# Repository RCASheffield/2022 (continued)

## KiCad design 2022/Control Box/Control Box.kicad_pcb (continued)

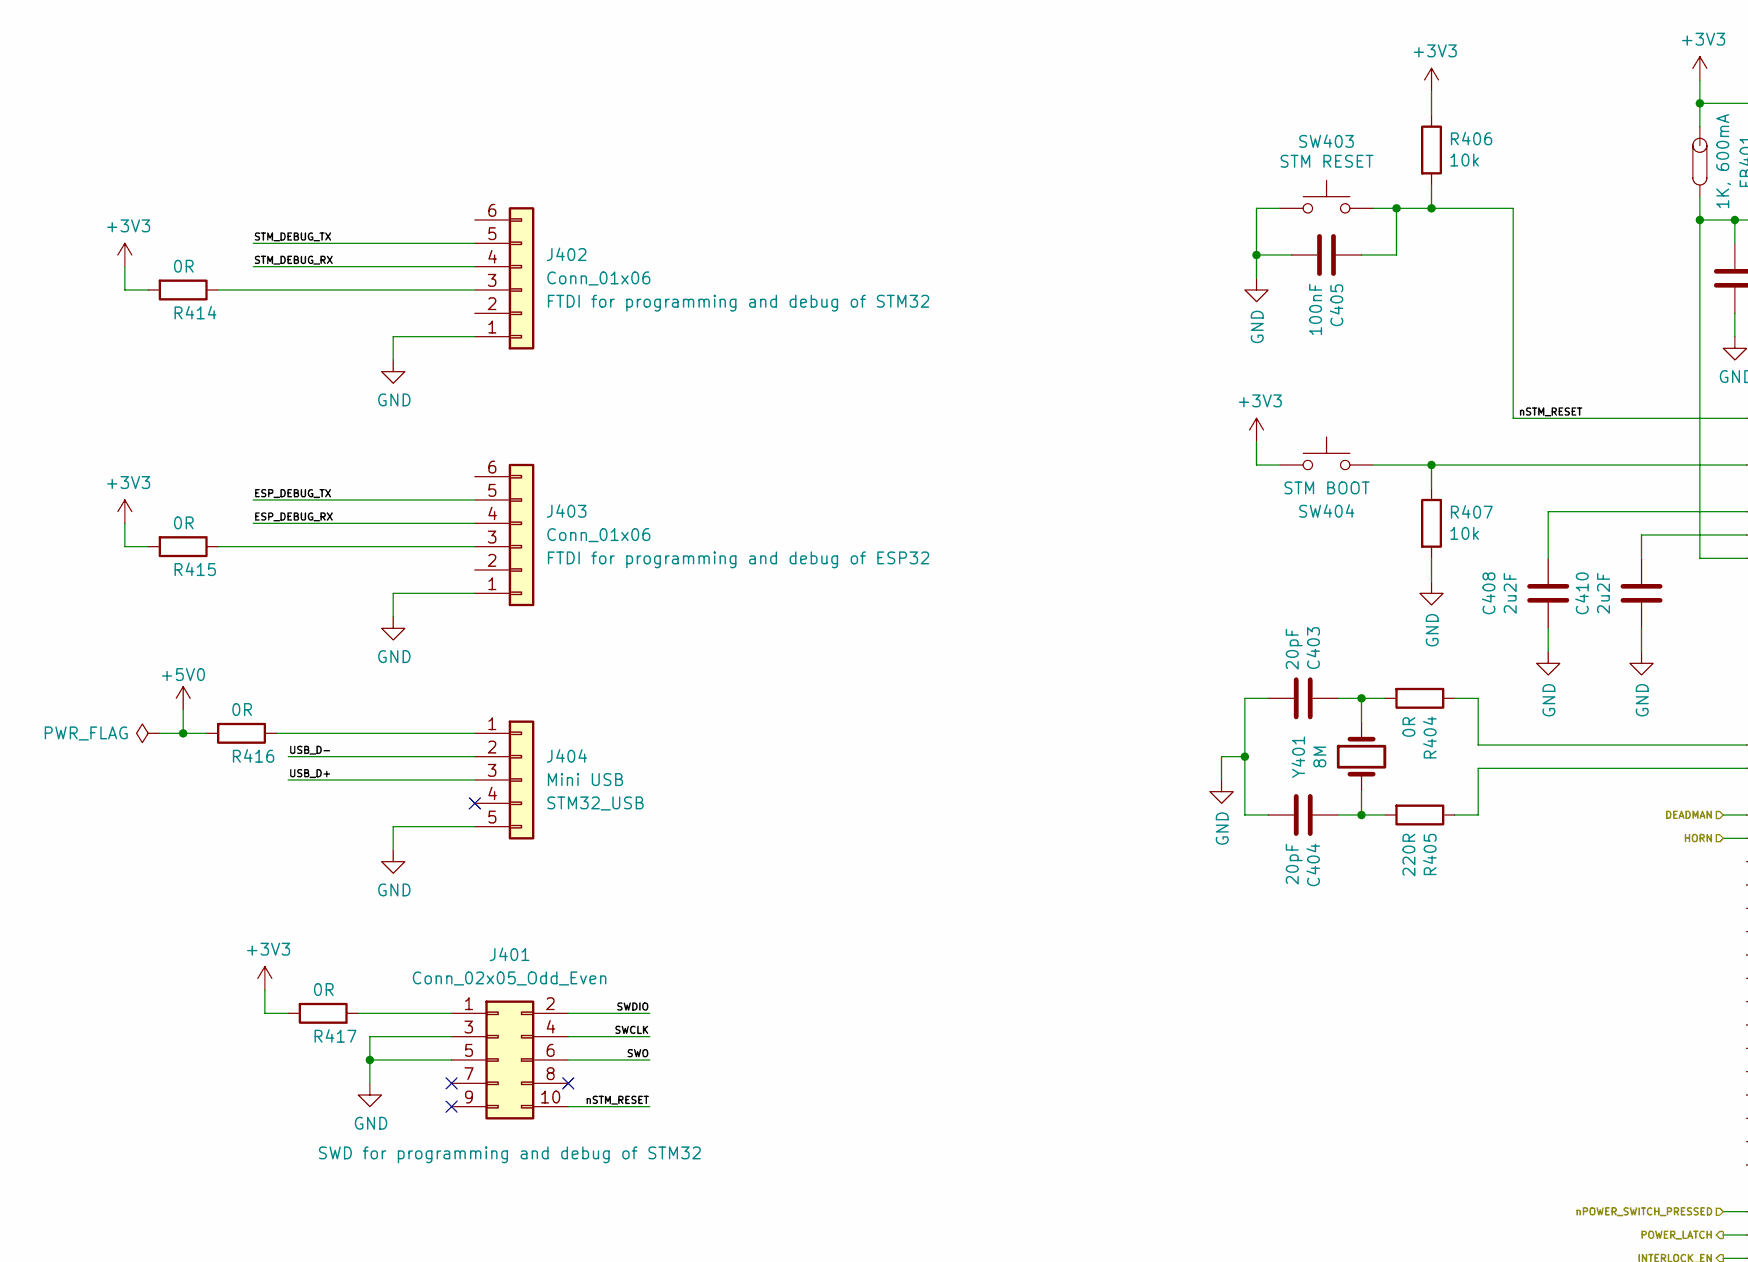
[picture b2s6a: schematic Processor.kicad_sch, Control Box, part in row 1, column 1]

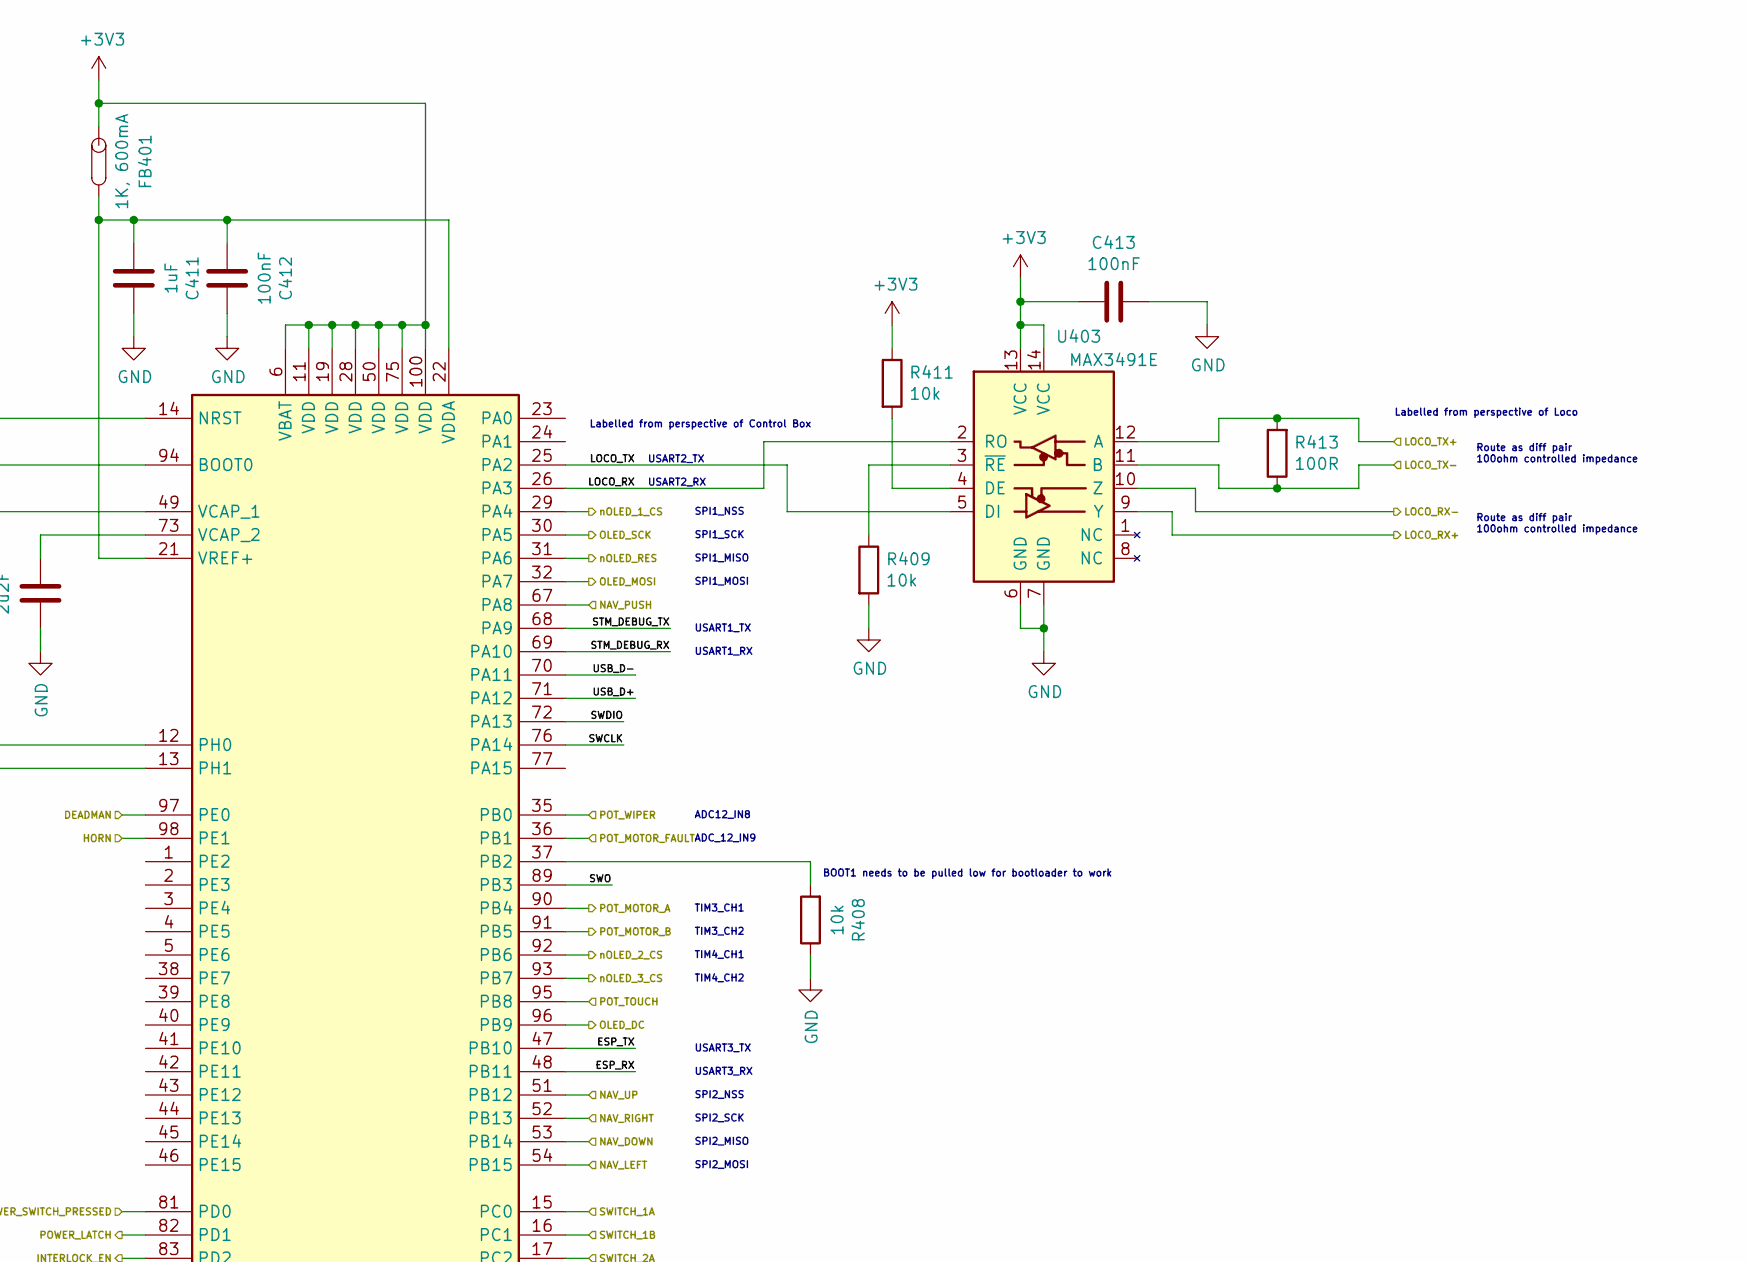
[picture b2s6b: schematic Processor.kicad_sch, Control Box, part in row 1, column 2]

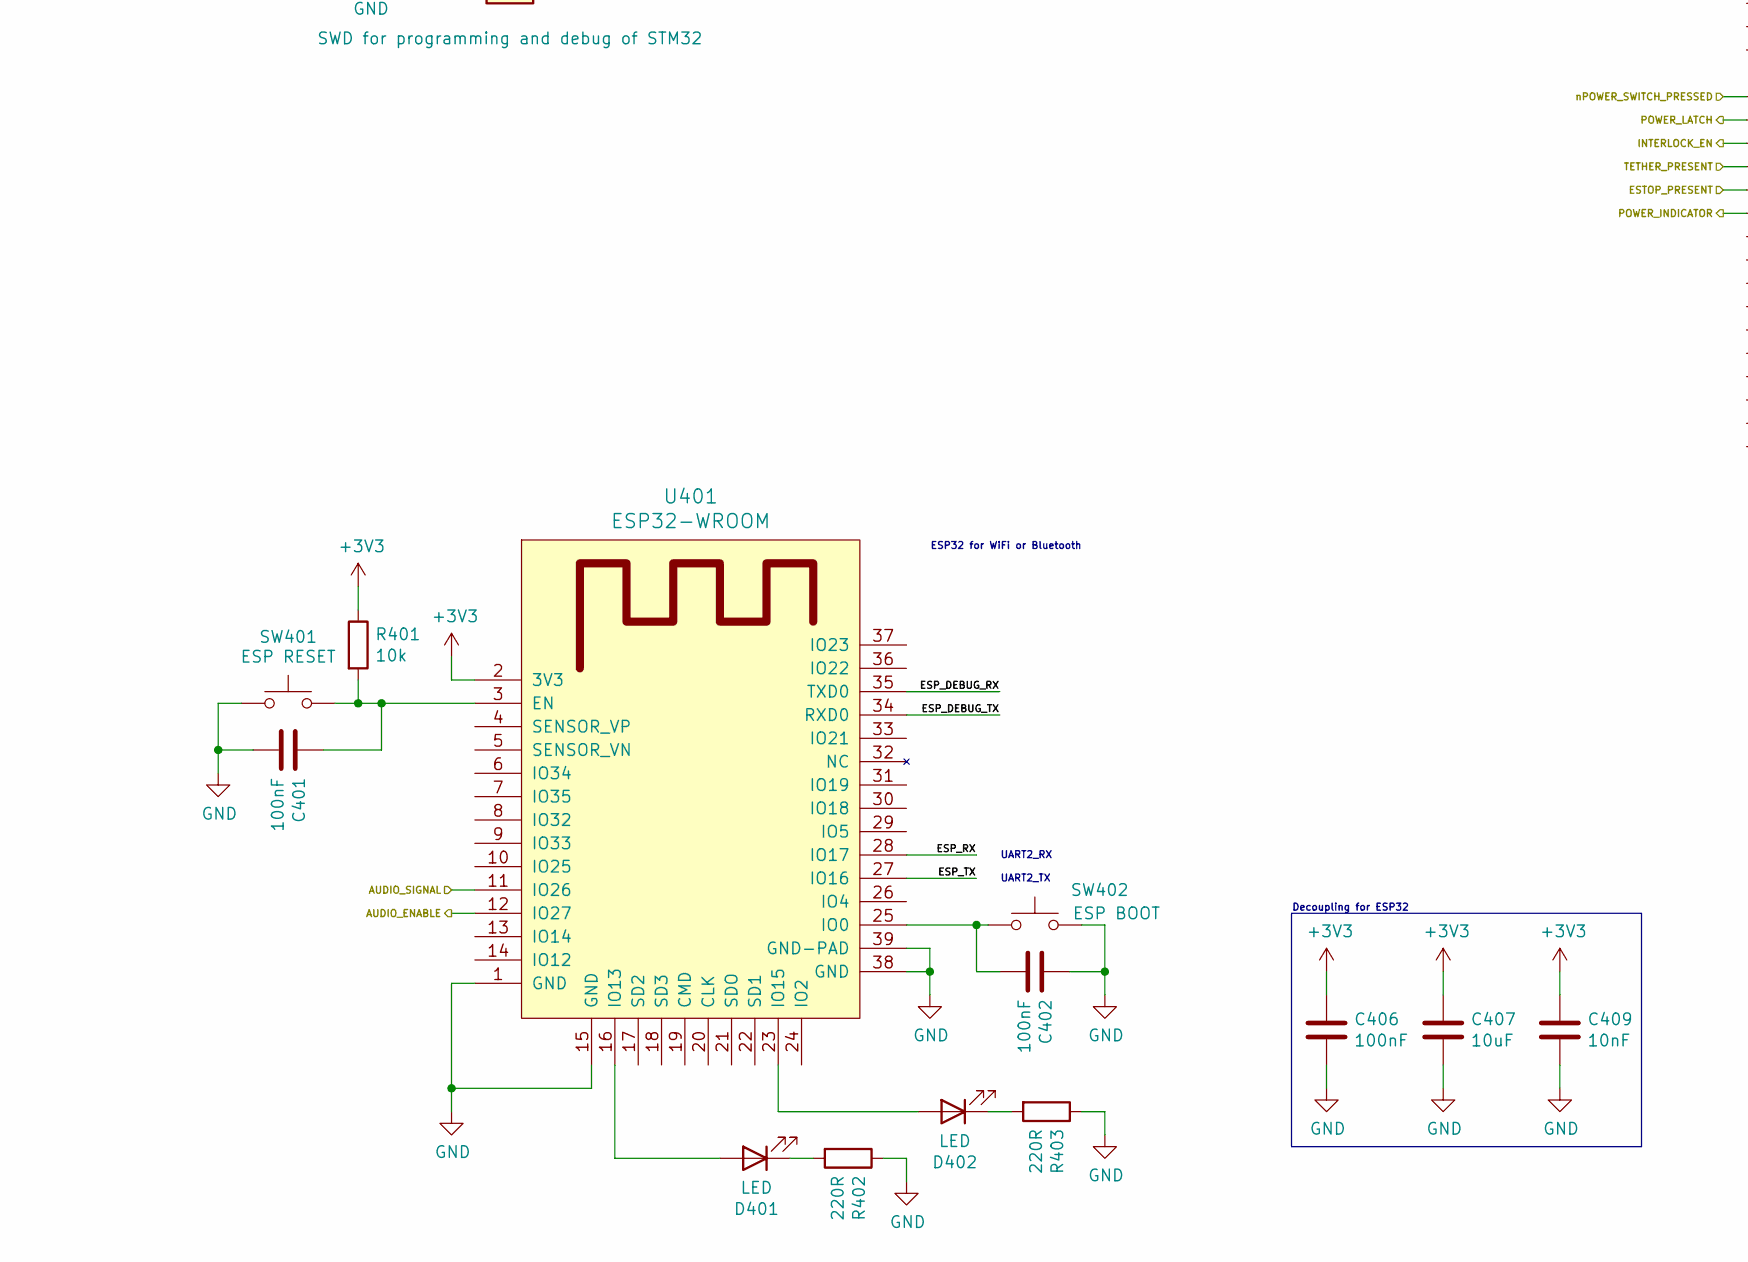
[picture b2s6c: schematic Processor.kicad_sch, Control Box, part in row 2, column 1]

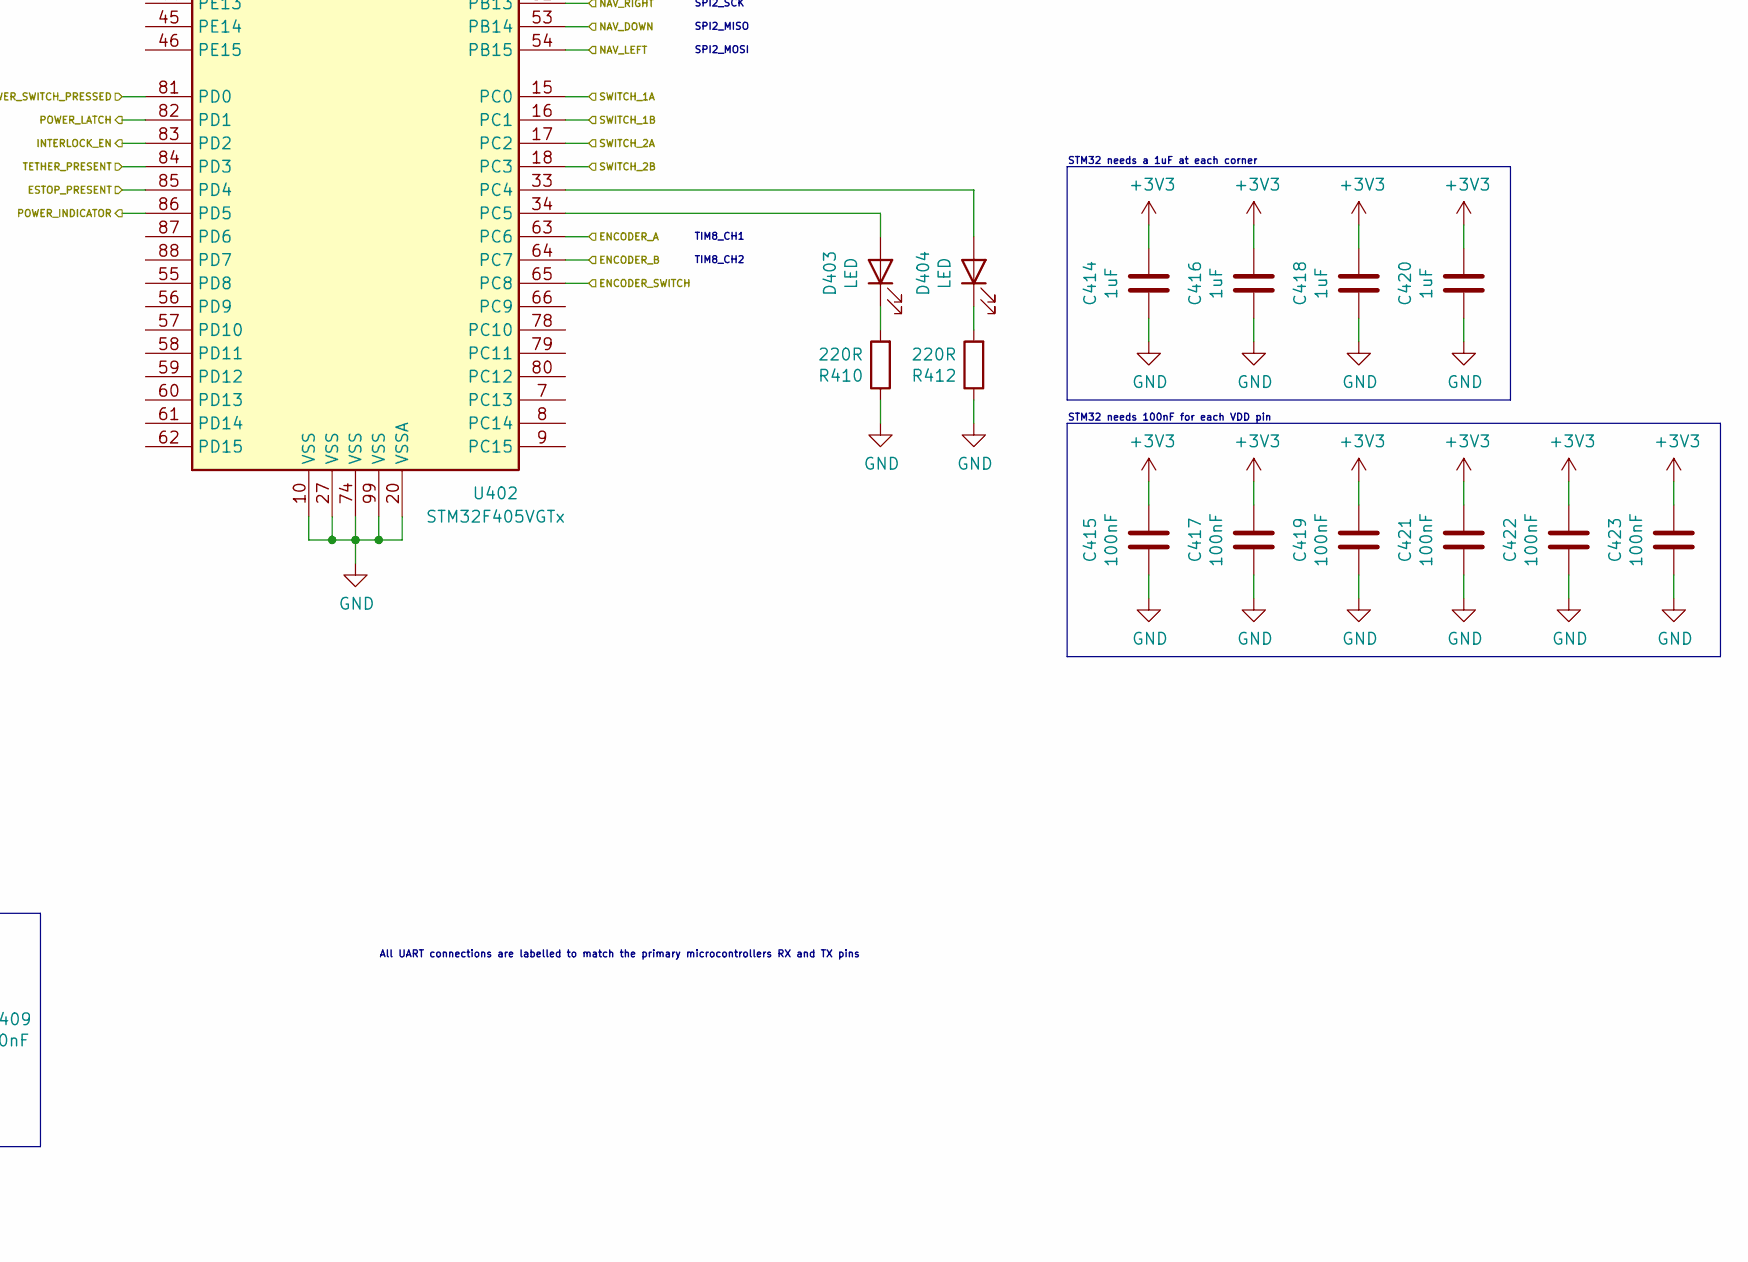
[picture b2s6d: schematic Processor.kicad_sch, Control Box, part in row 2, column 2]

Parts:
C401, C402, C405, C406, C412, C413, C415, C417, C419, C421, C422, C423: 100nF; C_0603_1608Metric; LCSC C14663
C403, C404: 20pF; C_0603_1608Metric; LCSC C1648
C407: 10uF; C_0603_1608Metric; LCSC C19702
C408, C410: 2u2F; C_0603_1608Metric; LCSC C23630
C409: 10nF; C_0603_1608Metric; LCSC C57112
C411, C414, C416, C418, C420: 1uF; C_0603_1608Metric; LCSC C15849
D401, D404: LED; LED_0603_1608Metric_Pad1.05x0.95mm_HandSolder; Manufacturer Part Number 150060YS75000; LCSC C205443
D402, D403: LED; LED_0603_1608Metric_Pad1.05x0.95mm_HandSolder; Manufacturer Part Number 150060YS75000; LCSC C2286
FB401: 1K, 600mA; L_0603_1608Metric_Pad1.05x0.95mm_HandSolder; Manufacturer Part Number 742792662; LCSC C85824
J401: Conn_02x05_Odd_Even; IDC-Header_2x05_P2.54mm_Vertical
J402, J403: Conn_01x06; PinHeader_1x06_P2.54mm_Vertical
J404: Mini USB; USB_Mini-B_Wuerth_65100516121_Horizontal; Manufacturer Part Number 0548191572
R401, R406, R407, R408, R409, R411: 10k; R_0603_1608Metric_Pad1.05x0.95mm_HandSolder; LCSC C25804
R402, R403, R405, R410, R412: 220R; R_0603_1608Metric_Pad1.05x0.95mm_HandSolder; LCSC C22962
R404: 0R; R_0603_1608Metric_Pad1.05x0.95mm_HandSolder; LCSC C21189
R413: 100R; R_0603_1608Metric_Pad1.05x0.95mm_HandSolder; LCSC C22775
R414, R415, R416, R417: 0R; R_1206_3216Metric_Pad1.42x1.75mm_HandSolder; LCSC C17888
SW401, SW402, SW403, SW404: SMD Tactile; SW_SPST_SKQG_WithoutStem; LCSC C318889
U401: ESP32-WROOM; Manufacturer Part Number ESP32-WROOM-32E
U402: STM32F405VGTx; LQFP-100_14x14mm_P0.5mm; LCSC C56621
U403: MAX3491E; SOIC-14_3.9x8.7mm_P1.27mm; Manufacturer Part Number MAX3491EESD; LCSC C61053
Y401: 8M; Crystal_SMD_5032-2Pin_5.0x3.2mm_HandSoldering; LCSC C115962

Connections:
+3V3: C406.1, C407.1, C409.1, C413.2, C414.1, C415.1, C416.1, C417.1, C418.1, C419.1, C420.1, C421.1, C422.1, C423.1, FB401.1, R401.1, R406.1, R411.1, R414.2, R415.2, R417.2, SW404.1, U401.2 (3V3), U402.6 (VBAT), U402.11 (VDD), U402.19 (VDD), U402.28 (VDD), U402.50 (VDD), U402.75 (VDD), U402.100 (VDD), U403.13 (VCC), U403.14 (VCC); also elsewhere on the board
+5V: R416.2; also elsewhere on the board
/Control Inputs/DEADMAN: U402.97 (PE0); also elsewhere on the board
/Control Inputs/ENCODER_A: U402.63 (PC6); also elsewhere on the board
/Control Inputs/ENCODER_B: U402.64 (PC7); also elsewhere on the board
/Control Inputs/ENCODER_SWITCH: U402.65 (PC8); also elsewhere on the board
/Control Inputs/HORN: U402.98 (PE1); also elsewhere on the board
/Control Inputs/NAV_DOWN: U402.53 (PB14); also elsewhere on the board
/Control Inputs/NAV_LEFT: U402.54 (PB15); also elsewhere on the board
/Control Inputs/NAV_PUSH: U402.67 (PA8); also elsewhere on the board
/Control Inputs/NAV_RIGHT: U402.52 (PB13); also elsewhere on the board
/Control Inputs/NAV_UP: U402.51 (PB12); also elsewhere on the board
/Control Inputs/POT_MOTOR_A: U402.90 (PB4); also elsewhere on the board
/Control Inputs/POT_MOTOR_B: U402.91 (PB5); also elsewhere on the board
/Control Inputs/POT_MOTOR_FAULT: U402.36 (PB1); also elsewhere on the board
/Control Inputs/POT_TOUCH: U402.95 (PB8); also elsewhere on the board
/Control Inputs/POT_WIPER: U402.35 (PB0); also elsewhere on the board
/Control Inputs/SWITCH_1A: U402.15 (PC0); also elsewhere on the board
/Control Inputs/SWITCH_1B: U402.16 (PC1); also elsewhere on the board
/Control Inputs/SWITCH_2A: U402.17 (PC2); also elsewhere on the board
/Control Inputs/SWITCH_2B: U402.18 (PC3); also elsewhere on the board
/Displays/AUDIO_ENABLE: U401.12 (IO27); also elsewhere on the board
/Displays/AUDIO_SIGNAL: U401.11 (IO26); also elsewhere on the board
/Displays/OLED_DC: U402.96 (PB9); also elsewhere on the board
/Displays/OLED_MOSI: U402.32 (PA7); also elsewhere on the board
/Displays/OLED_SCK: U402.30 (PA5); also elsewhere on the board
/Displays/nOLED_1_CS: U402.29 (PA4); also elsewhere on the board
/Displays/nOLED_2_CS: U402.92 (PB6); also elsewhere on the board
/Displays/nOLED_3_CS: U402.93 (PB7); also elsewhere on the board
/Displays/nOLED_RES: U402.31 (PA6); also elsewhere on the board
/LOCO_RX+: U403.9 (Y); also elsewhere on the board
/LOCO_RX-: U403.10 (Z); also elsewhere on the board
/LOCO_TX+: R413.2, U403.12 (A); also elsewhere on the board
/LOCO_TX-: R413.1, U403.11 (B); also elsewhere on the board
/Power & Interlocks/ESTOP_PRESENT: U402.85 (PD4); also elsewhere on the board
/Power & Interlocks/INTERLOCK_EN: U402.83 (PD2); also elsewhere on the board
/Power & Interlocks/POWER_INDICATOR: U402.86 (PD5); also elsewhere on the board
/Power & Interlocks/POWER_LATCH: U402.82 (PD1); also elsewhere on the board
/Power & Interlocks/TETHER_PRESENT: U402.84 (PD3); also elsewhere on the board
/Power & Interlocks/nPOWER_SWITCH_PRESSED: U402.81 (PD0); also elsewhere on the board
/Processor/ESP_DEBUG_RX: J403.4, U401.35 (TXD0)
/Processor/ESP_DEBUG_TX: J403.5, U401.34 (RXD0)
/Processor/ESP_RX: U401.28 (IO17), U402.48 (PB11)
/Processor/ESP_TX: U401.27 (IO16), U402.47 (PB10)
/Processor/LOCO_RX: U402.26 (PA3), U403.2 (RO)
/Processor/LOCO_TX: U402.25 (PA2), U403.5 (DI)
/Processor/STM_DEBUG_RX: J402.4, U402.69 (PA10)
/Processor/STM_DEBUG_TX: J402.5, U402.68 (PA9)
/Processor/SWCLK: J401.4, U402.76 (PA14)
/Processor/SWDIO: J401.2, U402.72 (PA13)
/Processor/SWO: J401.6, U402.89 (PB3)
/Processor/USB_D+: J404.3, U402.71 (PA12)
/Processor/USB_D-: J404.2, U402.70 (PA11)
/Processor/nSTM_RESET: C405.1, J401.10, R406.2, SW403.2, U402.14 (NRST)
GND: C401.2, C402.1, C403.2, C404.2, C405.2, C406.2, C407.2, C408.2, C409.2, C410.1, C411.2, C412.2, C413.1, C414.2, C415.2, C416.2, C417.2, C418.2, C419.2, C420.2, C421.2, C422.2, C423.2, J401.3, J401.5, J402.1, J403.1, J404.5, R402.1, R403.1, R407.2, R408.1, R409.2, R410.1, R412.1, SW401.1, SW402.2, SW403.1, U401.1 (GND), U401.15 (GND), U401.38 (GND), U401.39 (GND-PAD), U402.10 (VSS), U402.20 (VSSA), U402.27 (VSS), U402.74 (VSS), U402.99 (VSS), U403.6 (GND), U403.7 (GND); also elsewhere on the board
unnamed: C401.1, R401.2, SW401.2, U401.3 (EN)
unnamed: C402.2, SW402.1, U401.25 (IO0)
unnamed: C403.1, R404.2, Y401.1
unnamed: C404.1, R405.2, Y401.2
unnamed: C408.1, U402.49 (VCAP_1)
unnamed: C410.2, U402.73 (VCAP_2)
unnamed: C411.1, C412.1, FB401.2, U402.21 (VREF+), U402.22 (VDDA)
unnamed: D401.1 (K), R402.2
unnamed: D401.2 (A), U401.16 (IO13)
unnamed: D402.1 (K), R403.2
unnamed: D402.2 (A), U401.23 (IO15)
unnamed: D403.1 (K), R410.2
unnamed: D403.2 (A), U402.34 (PC5)
unnamed: D404.1 (K), R412.2
unnamed: D404.2 (A), U402.33 (PC4)
unnamed: J401.1, R417.1
unnamed: J402.3, R414.1
unnamed: J403.3, R415.1
unnamed: J404.1, R416.1
unnamed: R404.1, U402.12 (PH0)
unnamed: R405.1, U402.13 (PH1)
unnamed: R407.1, SW404.2, U402.94 (BOOT0)
unnamed: R408.2, U402.37 (PB2)
unnamed: R409.1, U403.3 (~RE)
unnamed: R411.2, U403.4 (DE)

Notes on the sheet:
USART2_RX
TIM4_CH2
ADC12_IN8
Labelled from perspective of Control Box
SPI1_MOSI
Route as diff pair 100ohm controlled impedance
SPI1_MISO
STM32 needs a 1uF at each corner
All UART connections are labelled to match the primary microcontrollers RX and TX pins
ADC_12_IN9
Labelled from perspective of Loco
USART2_TX
Decoupling for ESP32
SPI2_NSS
UART2_RX
TIM4_CH1
USART1_TX
UART2_TX
TIM8_CH2
SPI1_NSS
TIM3_CH2
USART3_TX
SPI2_SCK
TIM3_CH1
TIM8_CH1
ESP32 for WiFi or Bluetooth
BOOT1 needs to be pulled low for bootloader to work
USART1_RX
SPI1_SCK
SPI2_MOSI
STM32 needs 100nF for each VDD pin
SPI2_MISO
USART3_RX

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
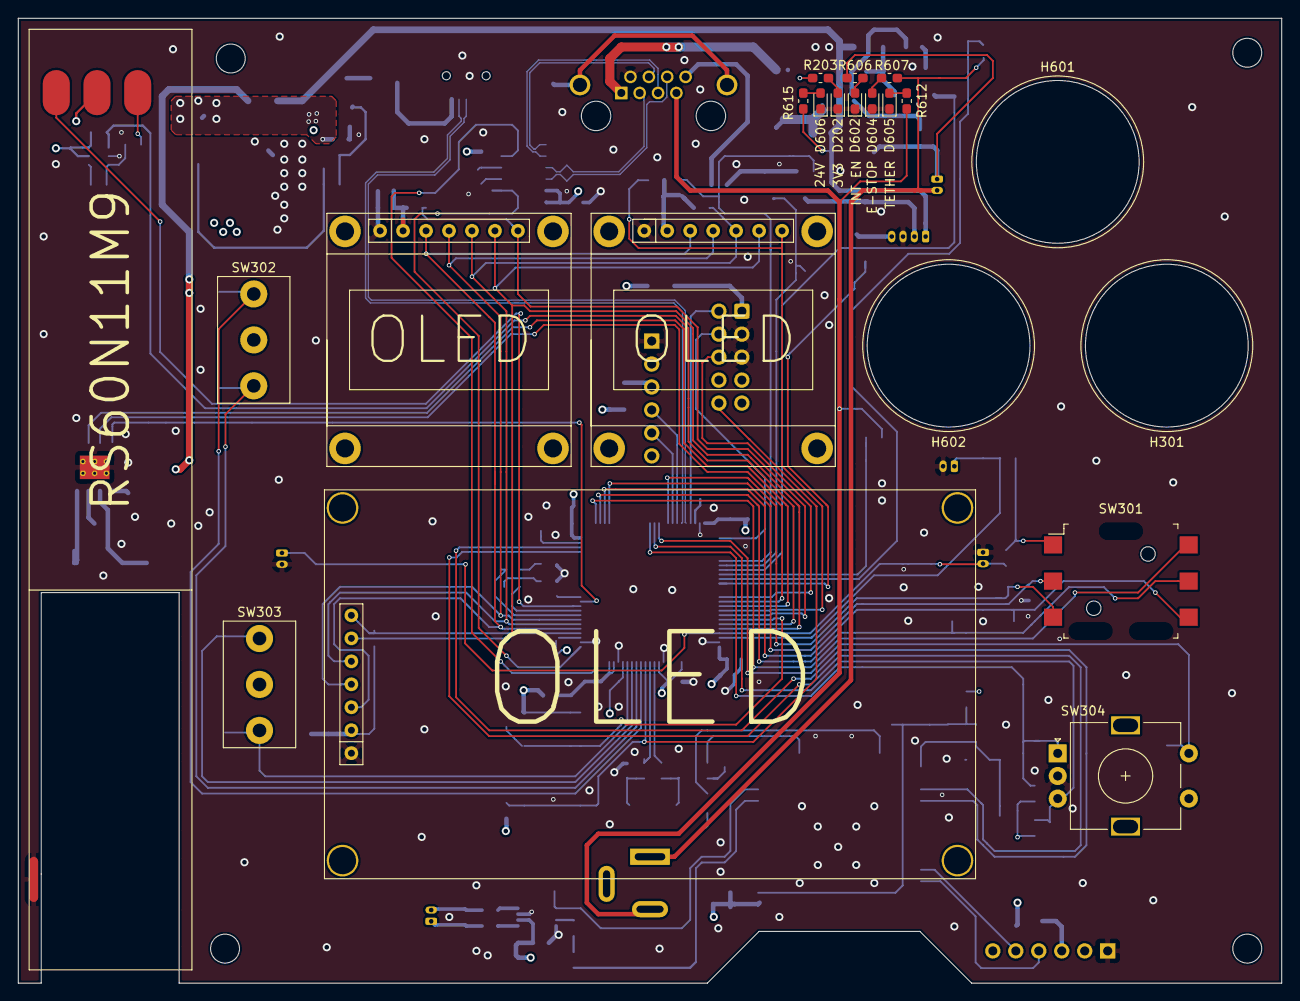
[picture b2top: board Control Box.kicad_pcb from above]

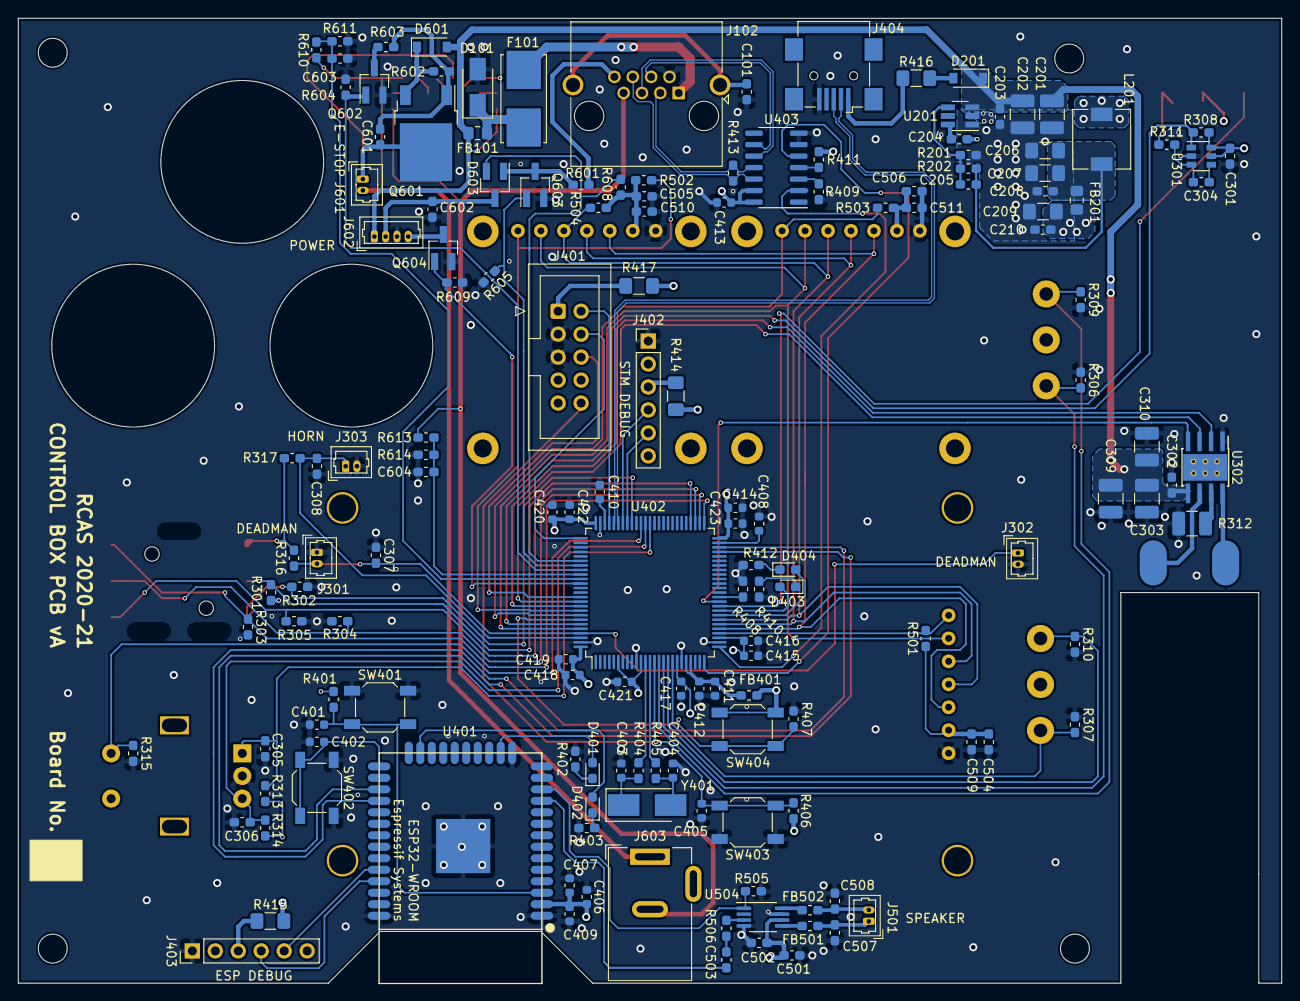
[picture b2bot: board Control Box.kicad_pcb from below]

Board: 4 copper layers, 139.7 x 106.7 mm, 180 parts (155 on the bottom side), 115 nets.

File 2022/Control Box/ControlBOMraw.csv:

"Id";"Designator";"Package";"Quantity";"Designation";"Supplier and ref";
1;"U502,U503";"0.96_OLED";2;"0.96_OLED_SPI";;;
2;"SW301";"Switch_Nav_12.4x12.4mm";1;"JS5208";;;
3;"SW304";"RotaryEncoder_Alps_EC11E-Switch_Vertical_H20mm";1;"EC11E1820402";;;
4;"SW302,SW303";"SW_Toggle_14x7mm";2;"SW_SPDT_MSM";;;
5;"P301";"Potentiometer_Motorised_RS60N11M9";1;"RS60N11M9";;;
6;"H101,H102,H103,H104";"MountingHole_3.2mm_M3";4;"M3";;;
7;"H301";"16mm_Blank_Button";1;"16mm Hole";;;
8;"H601";"16mm_E-STOP";1;"16mm Hole";;;
9;"H602";"16mm_Power_Button";1;"16mm Hole";;;
10;"J401";"IDC-Header_2x05_P2.54mm_Vertical";1;"Conn_02x05_Odd_Even";;;
11;"D604,D202,D605,D606,D602,D401,D402,D403,D404";"LED_0603_1608Metric_Pad1.05x0.95mm_HandSolder";9;"LED";;;
12;"R203,R402,R403,R405,R410,R412";"R_0603_1608Metric_Pad1.05x0.95mm_HandSolder";6;"220R";;;
13;"R612,R606,R615,R607";"R_0603_1608Metric_Pad1.05x0.95mm_HandSolder";4;"4k7";;;
14;"U501";"2.42_OLED";1;"2.42_OLED_SPI";;;
15;"R204";"R_0201_0603Metric";1;"0";;;
16;"U301";"SOT-23-6";1;"AT42QT1010-TSHR";;;
17;"U401";"ESP32-WROOM";1;"ESP32-WROOM";;;
18;"U504";"MSOP-8_3x3mm_P0.65mm";1;"PAM8302AAD";;;
19;"D101";"D_SMA";1;"26V, 9.5A";;;
20;"F101";"Fuseholder_Littelfuse_154";1;"Holder + 2A Fuse";;;
21;"FB101,FB201";"L_0805_2012Metric_Pad1.15x1.40mm_HandSolder";2;"600R, 2A";;;
22;"FB501,FB502,FB401";"L_0603_1608Metric_Pad1.05x0.95mm_HandSolder";3;"1K, 600mA";;;
23;"J301,J501,J302,J303,J601";"Molex_PicoBlade_53047-0210_1x02_P1.25mm_Vertical";5;"PicoBlade_1x02";;;
24;"J404";"USB_Mini-B_Wuerth_65100516121_Horizontal";1;"Mini USB";;;
25;"C301,C302,C305,C306,C509,C510,C511,C203,C204,C210,C603,C604";"C_0603_1608Metric_Pad1.05x0.95mm_HandSolder";12;"100nF";;;
26;"C304";"C_0603_1608Metric_Pad1.05x0.95mm_HandSolder";1;"22nF";;;
27;"C307,C308,C601,C602";"C_0603_1608Metric_Pad1.05x0.95mm_HandSolder";4;"1nF";;;
28;"C401,C402,C405,C406,C413,C415,C417,C419,C422,C421,C423,C412";"C_0603_1608Metric";12;"100nF";;;
29;"C403,C404";"C_0603_1608Metric";2;"20pF";;;
30;"C407";"C_0603_1608Metric";1;"10uF";;;
31;"C408,C410";"C_0603_1608Metric";2;"2u2F";;;
32;"C409";"C_0603_1608Metric";1;"10nF";;;
33;"C414,C418,C420,C416,C411";"C_0603_1608Metric";5;"1uF";;;
34;"C501,C503,C504,C505,C506";"C_0603_1608Metric_Pad1.05x0.95mm_HandSolder";5;"1uF";;;
35;"C502";"C_0603_1608Metric_Pad1.05x0.95mm_HandSolder";1;"10uF";;;
36;"C507,C508";"C_0603_1608Metric_Pad1.05x0.95mm_HandSolder";2;"220pF";;;
37;"D601,D201";"D_SOD-123";2;"1N5819HW-7-F";;;
38;"D603";"SOT-23_Handsoldering";1;"BAT54CL";;;
39;"J102";"RJ45_Amphenol_RJHSE5380";1;"RJ45";;;
40;"J603";"BarrelJack_Wuerth_6941xx301002";1;"Barrel Jack";;;
41;"Q601";"TO-252-2";1;"FQD11P06TM";;;
42;"Q602,Q603,Q604";"SOT-23_Handsoldering";3;"2N7002";;;
43;"R301,R302,R303,R304,R305,R306,R307,R308,R309,R310,R311,R313,R314,R315,R316,R317,R401,R406,R407,R408,R409,R411,R501,R502,R503,R504,R505,R602,R604,R605,R609,R611,R614,R608";"R_0603_1608Metric_Pad1.05x0.95mm_HandSolder";34;"10k";;;
44;"R312";"R_1210_3225Metric_Pad1.42x2.65mm_HandSolder";1;"330m";;;
45;"R404,R601";"R_0603_1608Metric_Pad1.05x0.95mm_HandSolder";2;"0R";;;
46;"R413,R506";"R_0603_1608Metric_Pad1.05x0.95mm_HandSolder";2;"100R";;;
47;"R414,R415,R417,R416";"R_1206_3216Metric_Pad1.42x1.75mm_HandSolder";4;"0R";;;
48;"U201";"SOT-23-6_Handsoldering";1;"TPS54202";;;
49;"C202,C303,C309,C310,C201";"C_1210_3225Metric_Pad1.42x2.65mm_HandSolder";5;"10uF";;;
50;"C205";"C_0603_1608Metric_Pad1.05x0.95mm_HandSolder";1;"56pF";;;
51;"C206,C207,C209";"C_1206_3216Metric_Pad1.42x1.75mm_HandSolder";3;"22uF";;;
52;"C208,C101";"C_0603_1608Metric_Pad1.05x0.95mm_HandSolder";2;"10nF";;;
53;"L201";"L_6.3x6.3_H3";1;"12uH";;;
54;"R201";"R_0603_1608Metric_Pad1.05x0.95mm_HandSolder";1;"22k1";;;
55;"R202";"R_0603_1608Metric_Pad1.05x0.95mm_HandSolder";1;"100k";;;
56;"SW401,SW402,SW403,SW404";"SW_SPST_SKQG_WithoutStem";4;"SMD Tactile";;;
57;"Y401";"Crystal_SMD_5032-2Pin_5.0x3.2mm_HandSoldering";1;"8M";;;
58;"R603";"R_0603_1608Metric_Pad1.05x0.95mm_HandSolder";1;"1k";;;
59;"R610,R613";"R_0603_1608Metric_Pad1.05x0.95mm_HandSolder";2;"68k";;;
60;"U403";"SOIC-14_3.9x8.7mm_P1.27mm";1;"MAX3491E";;;
61;"J402,J403";"PinHeader_1x06_P2.54mm_Vertical";2;"Conn_01x06";;;
62;"U402";"LQFP-100_14x14mm_P0.5mm";1;"STM32F405VGTx";;;
63;"J602";"Molex_PicoBlade_53047-0410_1x04_P1.25mm_Vertical";1;"PicoBlade_1x04";;;
64;"U302";"Texas_HTSOP-8-1EP_3.9x4.9mm_P1.27mm_EP2.95x4.9mm_Mask2.4x3.1mm_ThermalVias";1;"DRV8872DDA";;;

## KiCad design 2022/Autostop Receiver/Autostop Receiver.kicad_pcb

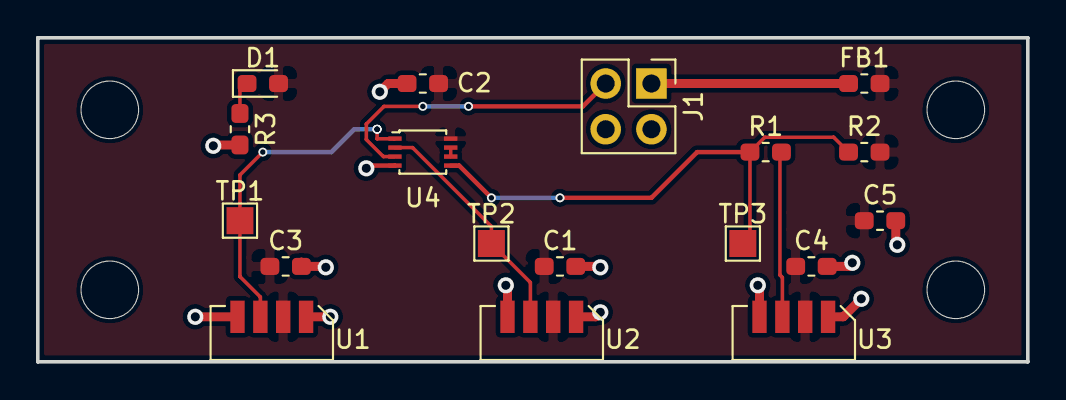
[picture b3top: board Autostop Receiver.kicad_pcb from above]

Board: 2 copper layers, 55.0 x 18.0 mm, 22 parts (0 on the bottom side), 10 nets.

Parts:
C1, C2, C3, C4: 100nF; C_0603_1608Metric_Pad1.05x0.95mm_HandSolder
C5: 10uF; C_0603_1608Metric_Pad1.05x0.95mm_HandSolder
D1: Green LED; LED_0603_1608Metric_Pad1.05x0.95mm_HandSolder
FB1: 1k, 600mA; L_0603_1608Metric_Pad1.05x0.95mm_HandSolder
H1, H2, H3, H4: M3; MountingHole_3.2mm_M3
J1: Header; PinHeader_2x02_P2.54mm_Vertical
R1: 0R; R_0603_1608Metric_Pad1.05x0.95mm_HandSolder
R2: 10k; R_0603_1608Metric_Pad1.05x0.95mm_HandSolder
R3: 1k; R_0603_1608Metric_Pad1.05x0.95mm_HandSolder
TP1, TP2: TestPoint; TestPoint_Pad_1.5x1.5mm
TP3: Test Point; TestPoint_Pad_1.5x1.5mm
U1, U2: TSOP75438; TSOP75xxx_IR_Receiver_Module
U3: TSOP75436; TSOP75xxx_IR_Receiver_Module
U4: SN74LVC2G132; VSSOP-8_2.4x2.1mm_P0.5mm

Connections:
+3V3: C1.1, C2.1, C3.1, C4.1, C5.1, D1.2, FB1.2, R2.2, U1.2, U2.2, U3.2, U4.8
/A.B+~C: J1.3, U4.3
/SENSOR_A: TP1.1, U1.3, U4.1
/SENSOR_B: TP2.1, U2.3, U4.2
/SENSOR_C: R1.1, R2.1, TP3.1, U4.5
/~A.B: U4.6, U4.7
GND: C1.2, C2.2, C3.2, C4.2, C5.2, J1.2, J1.4, R3.2, U1.1, U1.4, U2.1, U2.4, U3.1, U3.4, U4.4
unnamed: D1.1, R3.1
unnamed: FB1.1, J1.1
unnamed: R1.2, U3.3

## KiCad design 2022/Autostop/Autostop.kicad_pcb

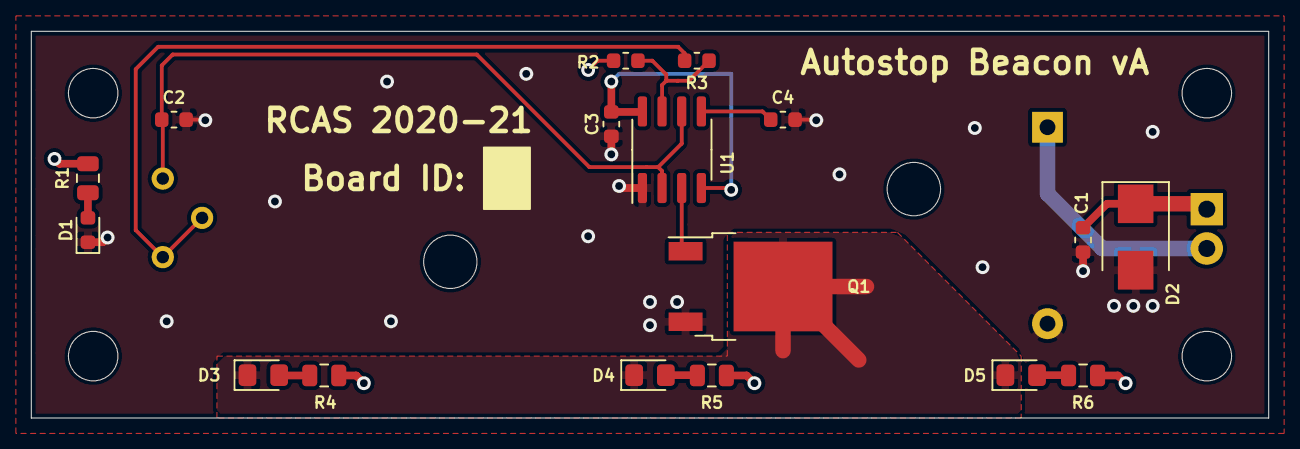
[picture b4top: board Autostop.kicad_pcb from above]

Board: 2 copper layers, 80.0 x 25.0 mm, 27 parts (0 on the bottom side), 13 nets.

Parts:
BT1: Battery; BatteryHolder_Keystone_2468_2xAAA
C1: 10uF; C_0603_1608Metric
C2: 470pF; C_0603_1608Metric
C3: 100nF; C_0603_1608Metric
C4: 10nF; C_0603_1608Metric
D1: LED; LED_0603_1608Metric
D2: D; D_SMB
D3, D4, D5: IR LED; LED_0805_2012Metric_Pad1.15x1.40mm_HandSolder
H1, H2, H3, H4: M3; MountingHole_3.2mm_M3
J1: Connector; TerminalBlock_TE_282834-2_1x02_P2.54mm_Horizontal
Q1: IRLR2703TRPBF; TO-252-2
R1: 100R; R_0805_2012Metric
R2: 1k; R_0603_1608Metric
R3: 39k; R_0603_1608Metric
R4, R5, R6: 22R; R_0805_2012Metric
RV1: 2k2; Potentiometer_Bourns_3296Y_Vertical
T1: Autostop Beacon vA; PCB_Title_&_Version
T3: RCAS 2020-21; RCAS_Year
T4: Board ID; Board_Number
U1: LMC555CM/NOPB; SOIC-8_3.9x4.9mm_P1.27mm

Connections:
+3V0: C1.1, C3.2, D2.1, J1.1, R1.2, R2.1, R4.1, R5.1, R6.1, U1.4, U1.8
GND: BT1.2, C1.2, C2.2, C3.1, C4.2, D1.1, D2.2, Q1.3, U1.1
unnamed: BT1.1, J1.2
unnamed: C2.1, RV1.3, U1.2, U1.6
unnamed: C4.1, U1.5
unnamed: D1.2, R1.1
unnamed: D3.1, D4.1, D5.1, Q1.2
unnamed: D3.2, R4.2
unnamed: D4.2, R5.2
unnamed: D5.2, R6.2
unnamed: Q1.1, U1.3
unnamed: R2.2, R3.1, U1.7
unnamed: R3.2, RV1.1, RV1.2

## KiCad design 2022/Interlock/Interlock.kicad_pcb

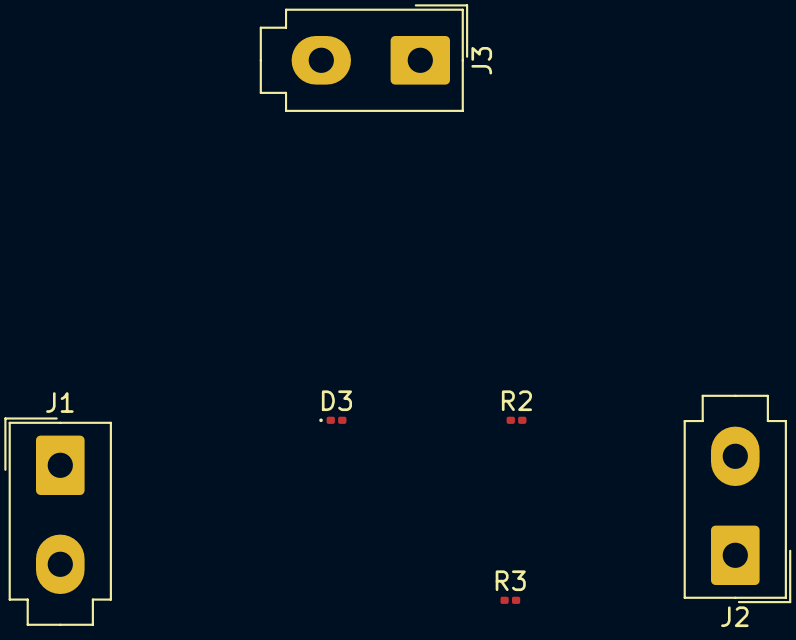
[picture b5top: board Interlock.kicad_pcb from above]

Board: 2 copper layers, 6 parts (0 on the bottom side), 3 nets, no tracks yet.

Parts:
D3: LED; D_0201_0603Metric
J1, J2, J3: Conn_01x02; Molex_Mini-Fit_Jr_5566-02A_2x01_P4.20mm_Vertical
R2, R3: Resistor; R_0201_0603Metric

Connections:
+3V3: J1.2, J2.1, R3.2
GND: D3.1 (K), J1.1, J2.2, R2.1
unnamed: J3.1, R2.2, R3.1

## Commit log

2022-03-01 Add files via upload
    Populating the new github
2022-03-01 Added manufacturing files folder
2022-03-01 BOM files
2022-03-04 Full Rework of PCB --> basically V2
2022-03-04 New fabrication files
2022-03-05 converted BOM&Place/BOM.csv to JLCPCB format with LCSC part numbers
2022-03-05 Updated BOM files - minor changes due to JLCPCB stock
2022-03-07 Removed buried vias
2022-03-15 trial
2022-03-22 choo choo year corrected
2022-03-29 Replaced 36KHz IR sensor with 56KHz
2022-04-09 interlock circuit
2022-04-10 Contorl Box commit
2022-04-10 trying to sort the github to upload the version on rcaspc2
2022-04-14 rewired pcb nee to sort diff pairs
2022-04-19 Added Loco test code in software folder
2022-04-22 Added Interlock PCB
2022-05-02 Added ethernet adapter
2022-05-03 Made changes to board layout
2022-05-03 Made changes to interlock pcb -jb
2022-05-06 Updated code
2022-05-10 TPM400 CAN test code
2022-05-10 had to repair git trying to push outputs folder over
2022-05-10 start of folder
2022-05-10 atttempt
2022-05-20 Control Box Ordering
2022-06-20 Control box code
